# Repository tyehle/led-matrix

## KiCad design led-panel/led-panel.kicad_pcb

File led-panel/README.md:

# 16x8 LED Matrix

Required parts: 128 of your favorite color 3mm LEDs, and a standard 24 pin header.

# Schematic

After putting the first one of these together I realized it might be better to solder all the LEDs in the other way around. this won't cause any issues with the wiring on the board and will play a little better with some of the schemes for driving LED panels.

# LICENSE

This work is licensed under a [Creative Commons Attribution-NonCommercial-ShareAlike 4.0 International License](http://creativecommons.org/licenses/by-nc-sa/4.0/).

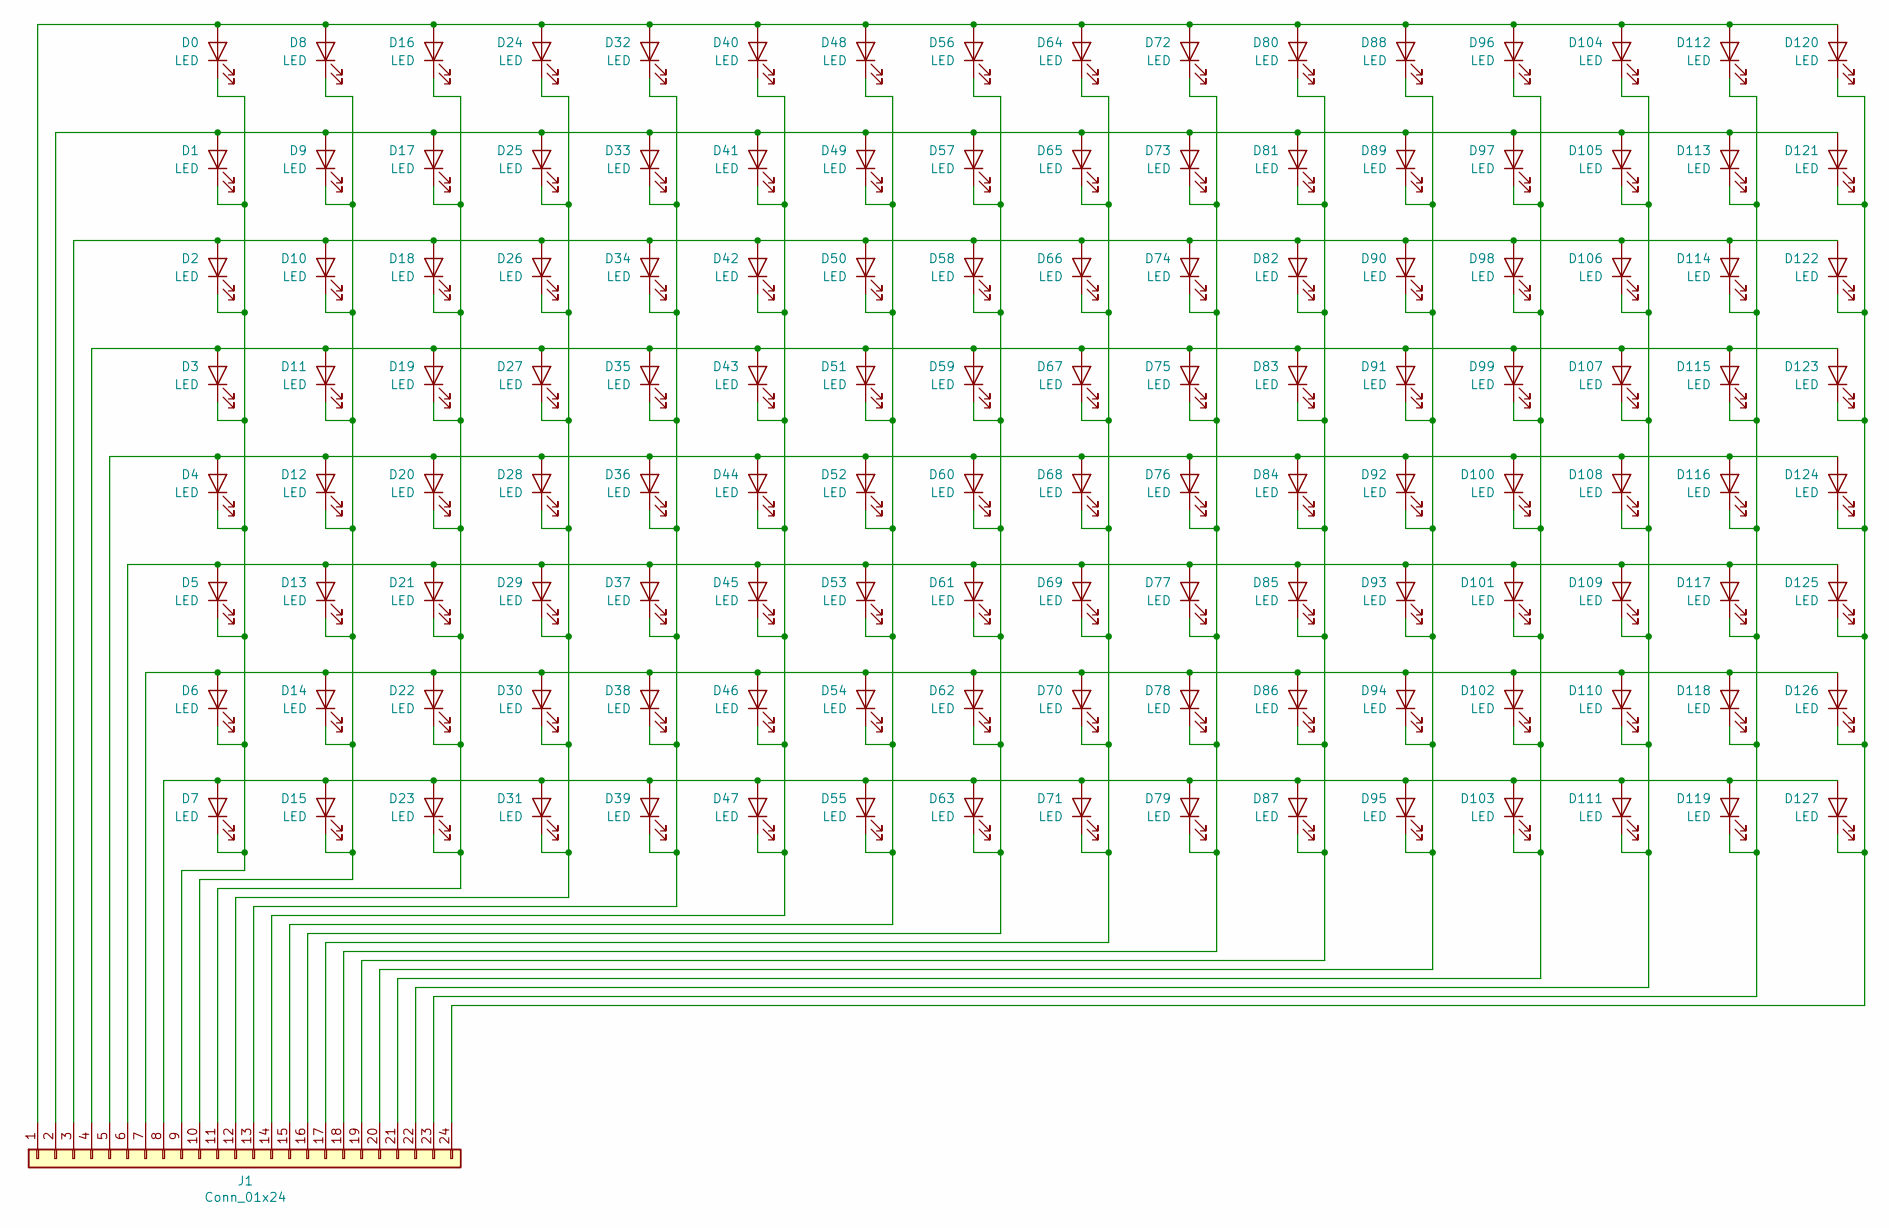
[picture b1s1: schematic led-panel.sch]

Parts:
D0, D1, D2, D3, D4, D5, D6, D7, D8, D9, D10, D11, D12, D13, D14, D15, D16, D17, D18, D19, D20, D21, D22, D23, D24, D25, D26, D27, D28, D29, D30, D31, D32, D33, D34, D35, D36, D37, D38, D39, D40, D41, D42, D43, D44, D45, D46, D47, D48, D49, D50, D51, D52, D53, D54, D55, D56, D57, D58, D59, D60, D61, D62, D63, D64, D65, D66, D67, D68, D69, D70, D71, D72, D73, D74, D75, D76, D77, D78, D79, D80, D81, D82, D83, D84, D85, D86, D87, D88, D89, D90, D91, D92, D93, D94, D95, D96, D97, D98, D99, D100, D101, D102, D103, D104, D105, D106, D107, D108, D109, D110, D111, D112, D113, D114, D115, D116, D117, D118, D119, D120, D121, D122, D123, D124, D125, D126, D127: LED; LED_D3.0mm
J1: Conn_01x24; PinHeader_1x8+16_P2.54mm_Vertical

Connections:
unnamed: D0.1 (K), D1.1 (K), D2.1 (K), D3.1 (K), D4.1 (K), D5.1 (K), D6.1 (K), D7.1 (K), J1.9
unnamed: D0.2 (A), D8.2 (A), D16.2 (A), D24.2 (A), D32.2 (A), D40.2 (A), D48.2 (A), D56.2 (A), D64.2 (A), D72.2 (A), D80.2 (A), D88.2 (A), D96.2 (A), D104.2 (A), D112.2 (A), D120.2 (A), J1.1
unnamed: D1.2 (A), D9.2 (A), D17.2 (A), D25.2 (A), D33.2 (A), D41.2 (A), D49.2 (A), D57.2 (A), D65.2 (A), D73.2 (A), D81.2 (A), D89.2 (A), D97.2 (A), D105.2 (A), D113.2 (A), D121.2 (A), J1.2
unnamed: D8.1 (K), D9.1 (K), D10.1 (K), D11.1 (K), D12.1 (K), D13.1 (K), D14.1 (K), D15.1 (K), J1.10
unnamed: D2.2 (A), D10.2 (A), D18.2 (A), D26.2 (A), D34.2 (A), D42.2 (A), D50.2 (A), D58.2 (A), D66.2 (A), D74.2 (A), D82.2 (A), D90.2 (A), D98.2 (A), D106.2 (A), D114.2 (A), D122.2 (A), J1.3
unnamed: D16.1 (K), D17.1 (K), D18.1 (K), D19.1 (K), D20.1 (K), D21.1 (K), D22.1 (K), D23.1 (K), J1.11
unnamed: D24.1 (K), D25.1 (K), D26.1 (K), D27.1 (K), D28.1 (K), D29.1 (K), D30.1 (K), D31.1 (K), J1.12
unnamed: D32.1 (K), D33.1 (K), D34.1 (K), D35.1 (K), D36.1 (K), D37.1 (K), D38.1 (K), D39.1 (K), J1.13
unnamed: D40.1 (K), D41.1 (K), D42.1 (K), D43.1 (K), D44.1 (K), D45.1 (K), D46.1 (K), D47.1 (K), J1.14
unnamed: D48.1 (K), D49.1 (K), D50.1 (K), D51.1 (K), D52.1 (K), D53.1 (K), D54.1 (K), D55.1 (K), J1.15
unnamed: D56.1 (K), D57.1 (K), D58.1 (K), D59.1 (K), D60.1 (K), D61.1 (K), D62.1 (K), D63.1 (K), J1.16
unnamed: D64.1 (K), D65.1 (K), D66.1 (K), D67.1 (K), D68.1 (K), D69.1 (K), D70.1 (K), D71.1 (K), J1.17
unnamed: D72.1 (K), D73.1 (K), D74.1 (K), D75.1 (K), D76.1 (K), D77.1 (K), D78.1 (K), D79.1 (K), J1.18
unnamed: D80.1 (K), D81.1 (K), D82.1 (K), D83.1 (K), D84.1 (K), D85.1 (K), D86.1 (K), D87.1 (K), J1.19
unnamed: D88.1 (K), D89.1 (K), D90.1 (K), D91.1 (K), D92.1 (K), D93.1 (K), D94.1 (K), D95.1 (K), J1.20
unnamed: D96.1 (K), D97.1 (K), D98.1 (K), D99.1 (K), D100.1 (K), D101.1 (K), D102.1 (K), D103.1 (K), J1.21
unnamed: D4.2 (A), D12.2 (A), D20.2 (A), D28.2 (A), D36.2 (A), D44.2 (A), D52.2 (A), D60.2 (A), D68.2 (A), D76.2 (A), D84.2 (A), D92.2 (A), D100.2 (A), D108.2 (A), D116.2 (A), D124.2 (A), J1.5
unnamed: D5.2 (A), D13.2 (A), D21.2 (A), D29.2 (A), D37.2 (A), D45.2 (A), D53.2 (A), D61.2 (A), D69.2 (A), D77.2 (A), D85.2 (A), D93.2 (A), D101.2 (A), D109.2 (A), D117.2 (A), D125.2 (A), J1.6
unnamed: D6.2 (A), D14.2 (A), D22.2 (A), D30.2 (A), D38.2 (A), D46.2 (A), D54.2 (A), D62.2 (A), D70.2 (A), D78.2 (A), D86.2 (A), D94.2 (A), D102.2 (A), D110.2 (A), D118.2 (A), D126.2 (A), J1.7
unnamed: D7.2 (A), D15.2 (A), D23.2 (A), D31.2 (A), D39.2 (A), D47.2 (A), D55.2 (A), D63.2 (A), D71.2 (A), D79.2 (A), D87.2 (A), D95.2 (A), D103.2 (A), D111.2 (A), D119.2 (A), D127.2 (A), J1.8
unnamed: D104.1 (K), D105.1 (K), D106.1 (K), D107.1 (K), D108.1 (K), D109.1 (K), D110.1 (K), D111.1 (K), J1.22
unnamed: D3.2 (A), D11.2 (A), D19.2 (A), D27.2 (A), D35.2 (A), D43.2 (A), D51.2 (A), D59.2 (A), D67.2 (A), D75.2 (A), D83.2 (A), D91.2 (A), D99.2 (A), D107.2 (A), D115.2 (A), D123.2 (A), J1.4
unnamed: D112.1 (K), D113.1 (K), D114.1 (K), D115.1 (K), D116.1 (K), D117.1 (K), D118.1 (K), D119.1 (K), J1.23
unnamed: D120.1 (K), D121.1 (K), D122.1 (K), D123.1 (K), D124.1 (K), D125.1 (K), D126.1 (K), D127.1 (K), J1.24

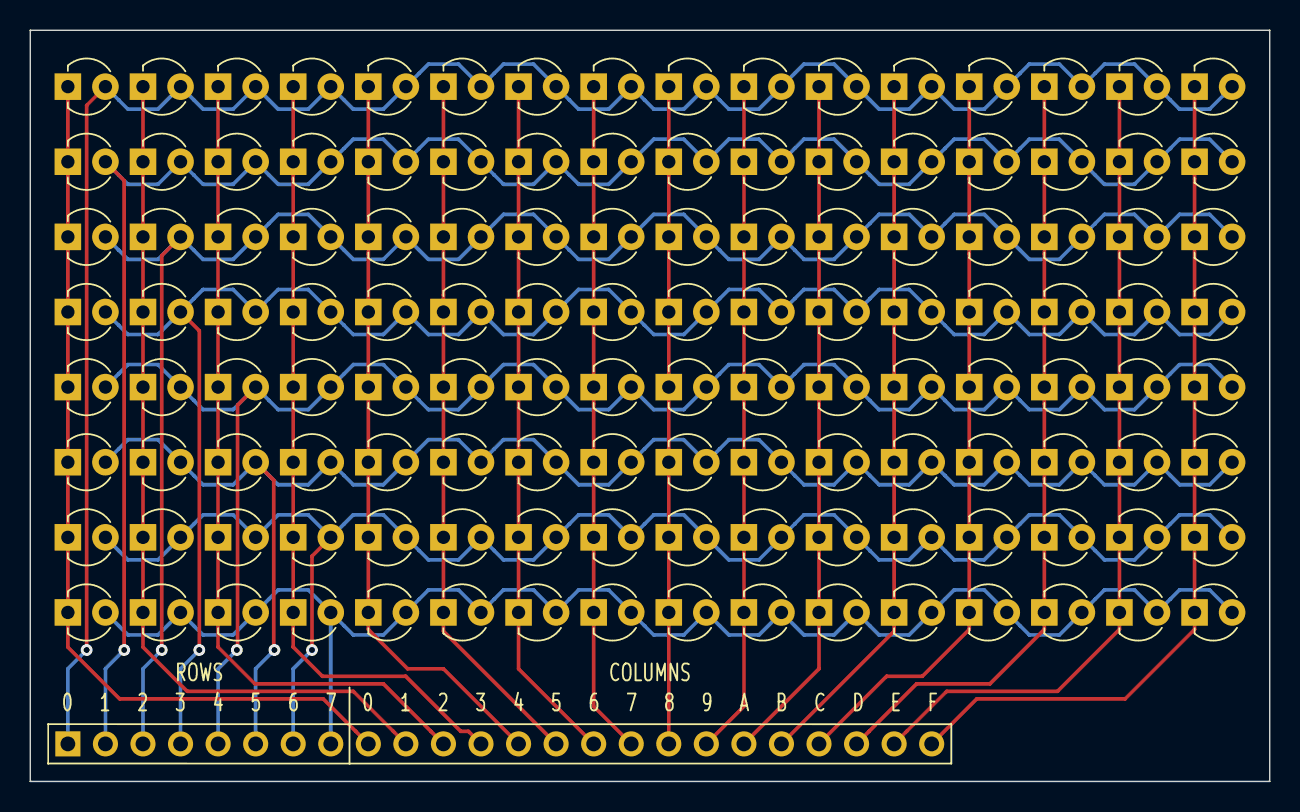
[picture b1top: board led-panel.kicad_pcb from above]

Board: 2 copper layers, 83.8 x 50.8 mm, 129 parts (0 on the bottom side), 24 nets.

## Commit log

2019-11-13 snake led matrix code
2019-11-20 add brightness control
2019-11-20 normalize and reduce the brightness levels
2019-11-20 kicad panel project
2019-11-20 components chosen
2019-11-21 schematic for an 8x16 panel
2019-11-21 components arranged
2019-11-21 hide all led labels
2019-11-21 properly ignore files
2019-11-21 routing done
2019-11-21 generate gerbers
2019-11-21 fix the routing
2019-11-21 remove bad gerbers
2019-11-22 update header footprint silkscreen
2019-11-22 fix led silkscreen
2019-11-22 add ascii neo
2019-11-22 add svg renders
2019-11-22 add a readme
2019-11-22 Update README.md
    fix images in readme
2020-01-16 full board hilbert curve
2020-01-16 clean up old code
2020-01-16 smooth the tail
2020-01-16 use shift registers to drive the matrix
2020-01-16 shift register poc
2020-01-16 use the decoder chip
2020-05-05 Update README.md
    add a note about flipping the LEDs
